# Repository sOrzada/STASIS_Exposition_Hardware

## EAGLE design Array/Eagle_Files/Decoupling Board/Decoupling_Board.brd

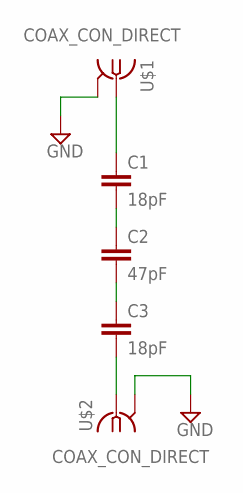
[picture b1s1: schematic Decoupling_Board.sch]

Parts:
C1, C3: 18pF; C1210
C2: 47pF; C1210
U$1, U$2: COAX_CON_DIRECT; COAX.141

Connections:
GND: U$1.P$2 (GND), U$2.P$2 (GND)
unnamed: C1.1, U$1.P$1 (1)
unnamed: C1.2, C2.1
unnamed: C2.2, C3.1
unnamed: C3.2, U$2.P$1 (1)

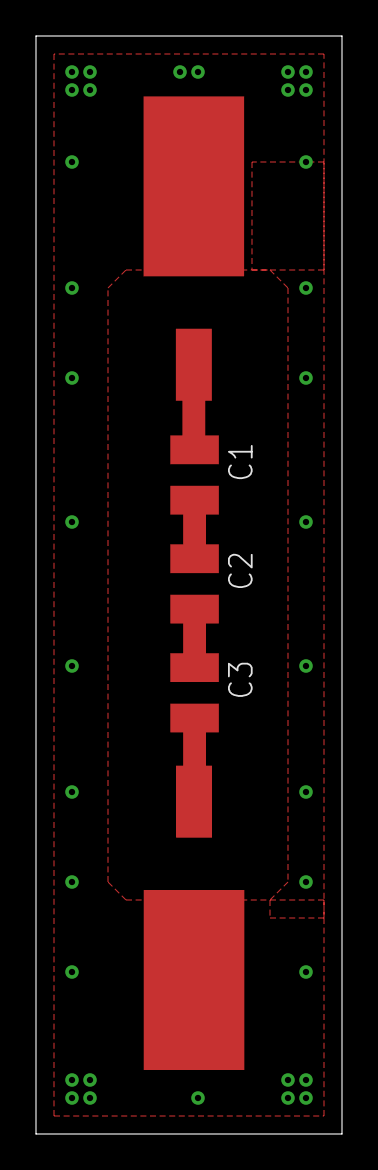
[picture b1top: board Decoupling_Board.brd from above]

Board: 2 copper layers, 17.0 x 61.0 mm, 5 parts (0 on the bottom side), 5 nets.

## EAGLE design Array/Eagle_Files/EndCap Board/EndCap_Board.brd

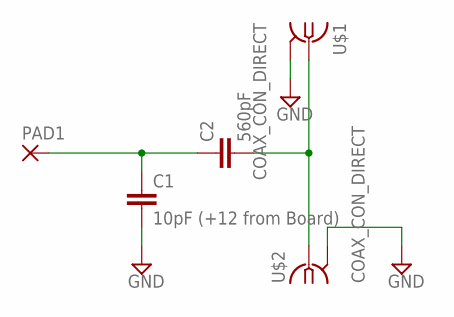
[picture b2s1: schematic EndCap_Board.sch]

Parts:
C1: 10pF (+12 from Board); C1210
C2: 560pF; C1210
PAD1: SMD5; SMD2,54-5,08
U$1, U$2: COAX_CON_DIRECT; COAX.141

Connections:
GND: C1.2, U$1.P$2 (GND), U$2.P$2 (GND)
unnamed: C1.1, C2.1, PAD1.1
unnamed: C2.2, U$1.P$1 (1), U$2.P$1 (1)

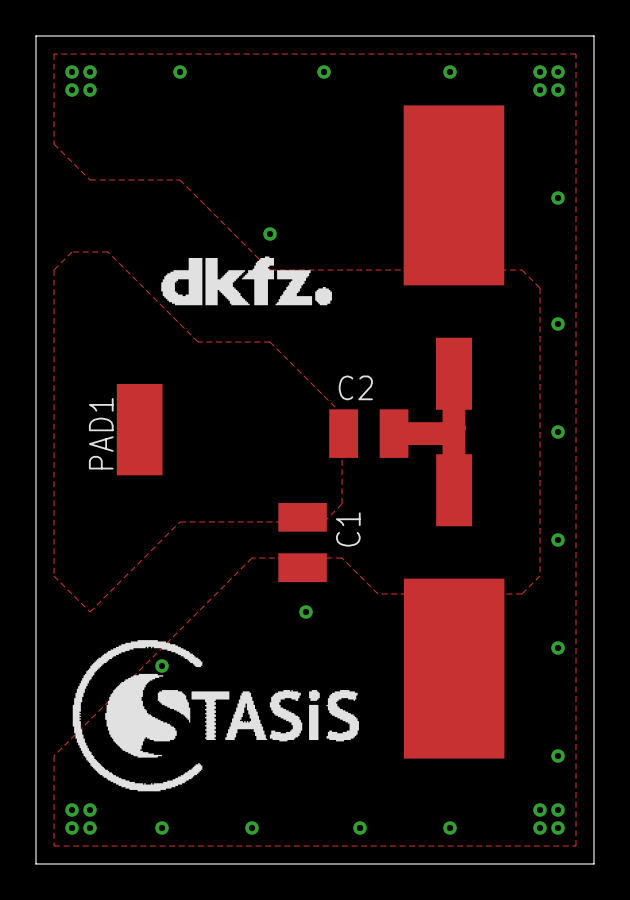
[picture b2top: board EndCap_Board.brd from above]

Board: 2 copper layers, 31.0 x 46.0 mm, 7 parts (0 on the bottom side), 3 nets.

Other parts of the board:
U$3: LOGO_STASIS
U$4: LOGO_DKFZ

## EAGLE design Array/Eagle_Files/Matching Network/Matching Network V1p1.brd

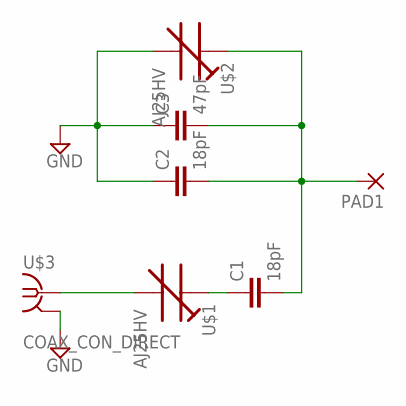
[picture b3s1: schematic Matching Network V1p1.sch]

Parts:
C1, C2: 18pF; C1210
C3: 47pF; C1210
PAD1: SMD5; SMD2,54-5,08
U$1, U$2: AJ25HV
U$3: COAX_CON_DIRECT; COAX.141

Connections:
GND: C2.1, C3.1, U$2.P$1 (A), U$3.P$2 (GND)
unnamed: C1.1, U$1.P$2 (E)
unnamed: C1.2, C2.2, C3.2, PAD1.1, U$2.P$2 (E)
unnamed: U$1.P$1 (A), U$3.P$1 (1)

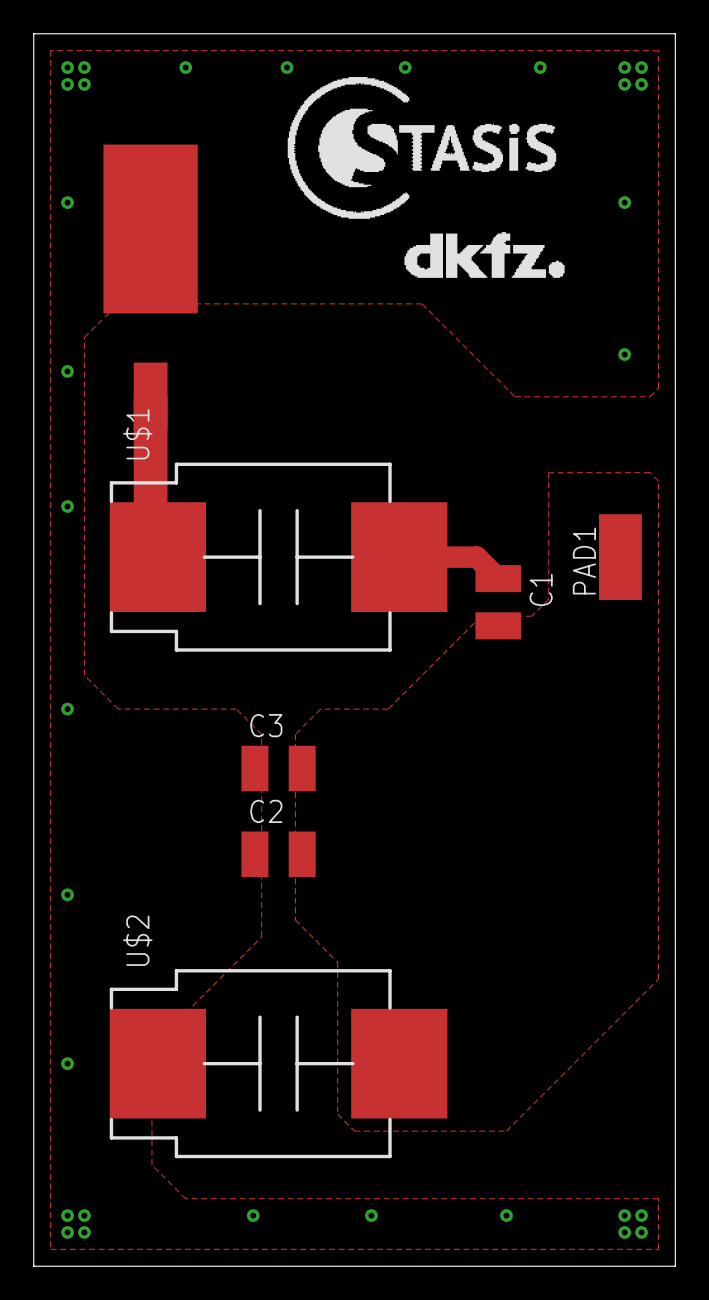
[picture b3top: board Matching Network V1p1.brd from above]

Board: 2 copper layers, 38.0 x 73.0 mm, 9 parts (0 on the bottom side), 4 nets.

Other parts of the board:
U$4: LOGO_STASIS
U$5: LOGO_DKFZ

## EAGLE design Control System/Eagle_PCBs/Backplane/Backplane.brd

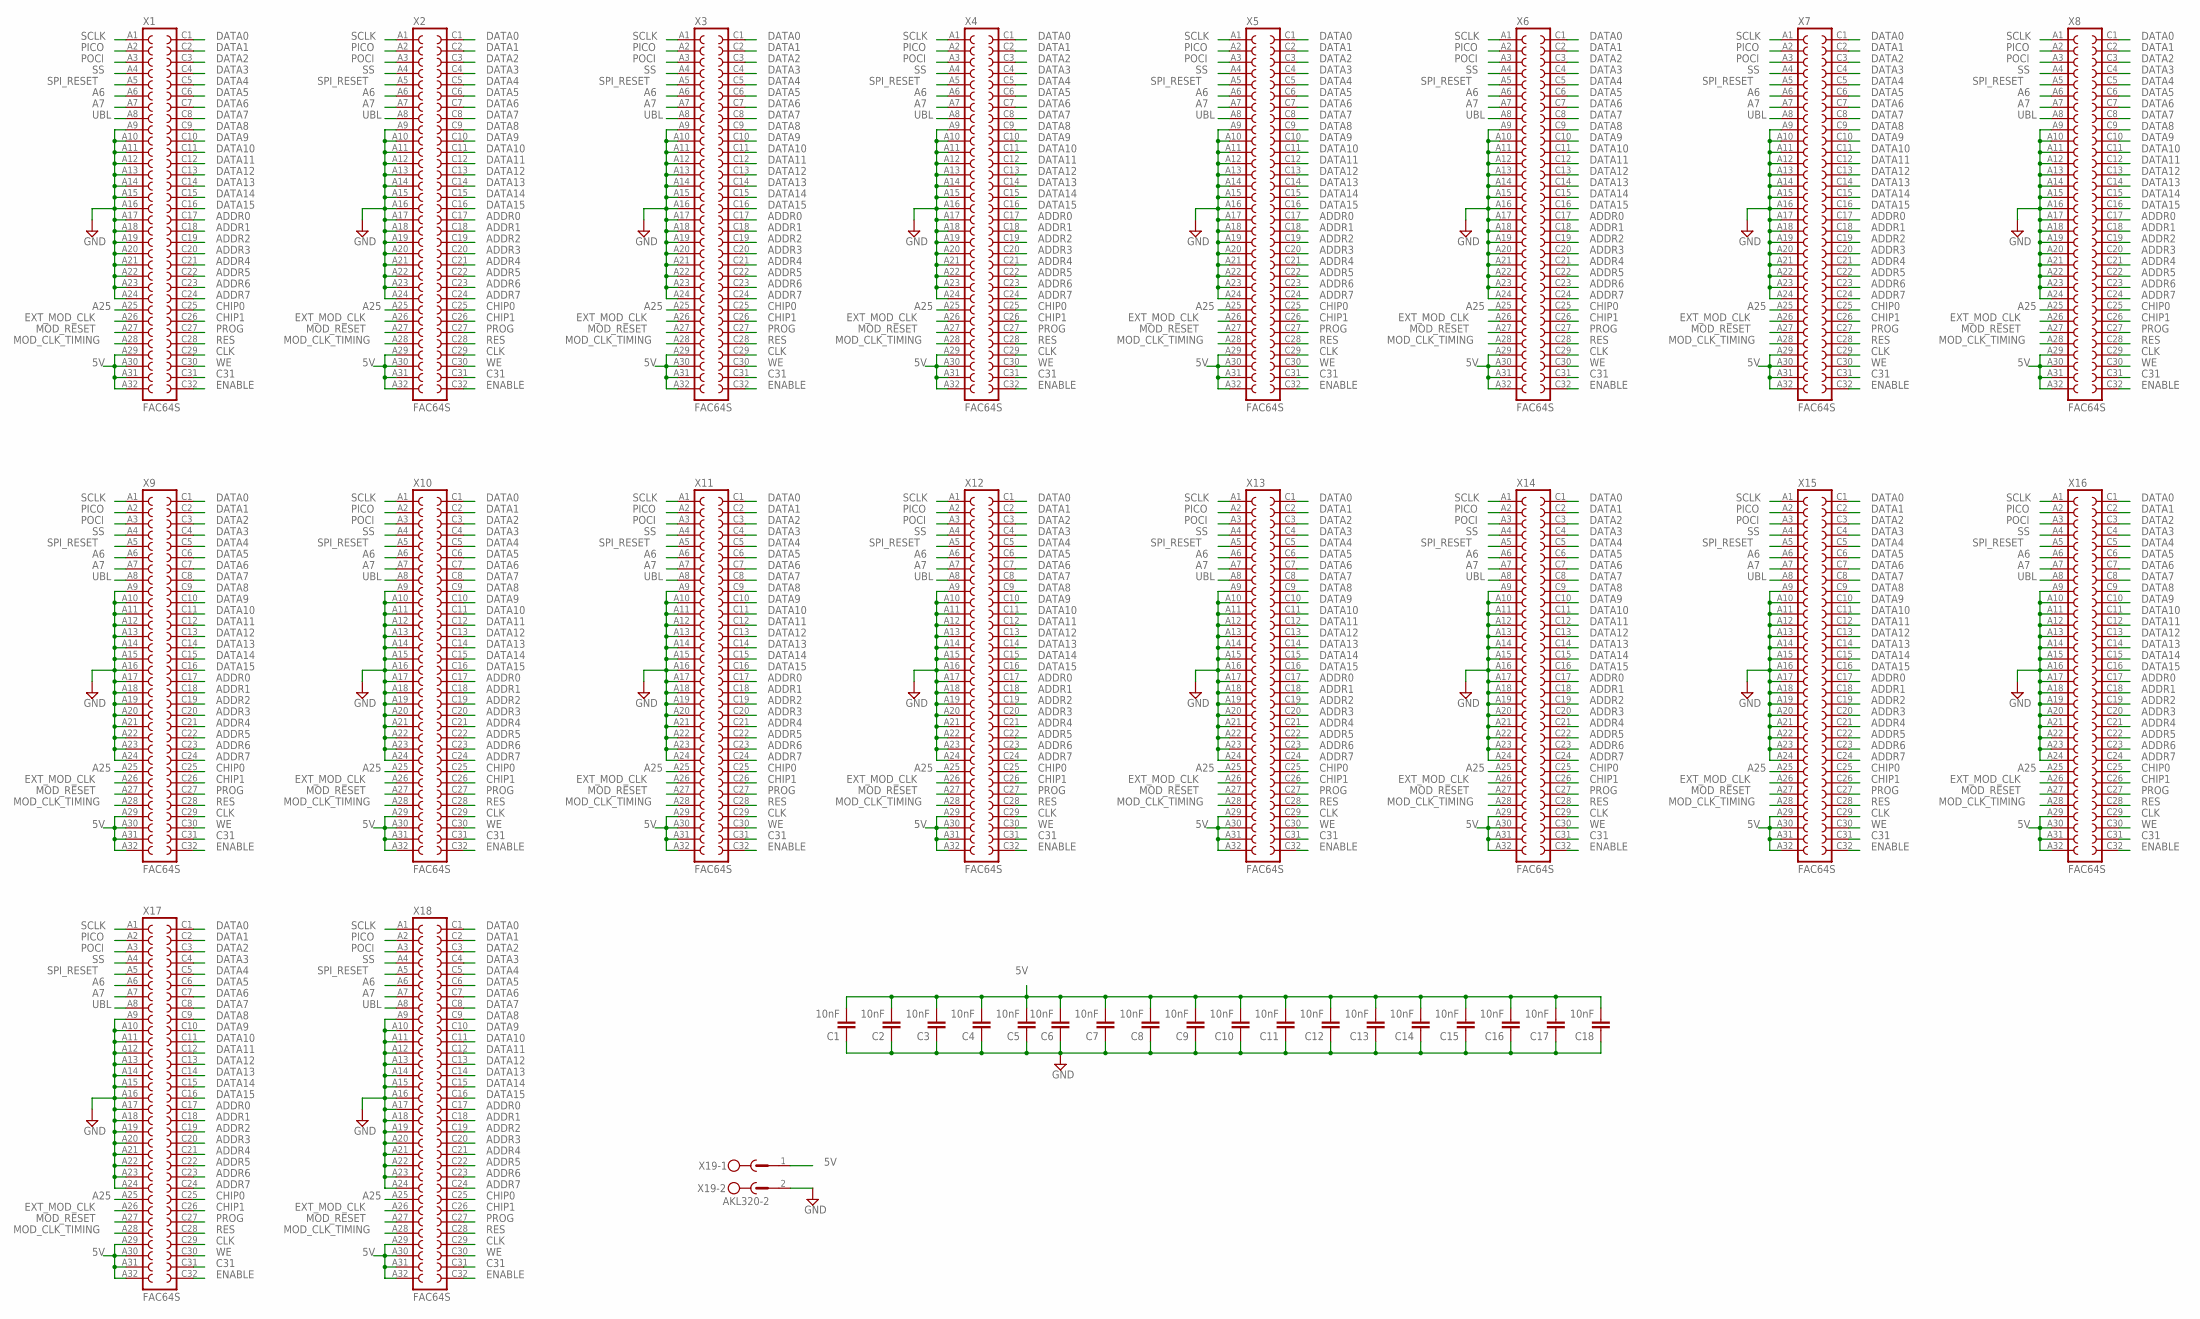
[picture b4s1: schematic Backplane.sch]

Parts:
C1, C2, C3, C4, C5, C6, C7, C8, C9, C10, C11, C12, C13, C14, C15, C16, C17, C18: 10nF; C0603
X1, X2, X3, X4, X5, X6, X7, X8, X9, X10, X11, X12, X13, X14, X15, X16, X17, X18: FAC64S
X19: AKL320-2; MSTBV2

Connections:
5V: C1.2, C2.2, C3.2, C4.2, C5.2, C6.2, C7.2, C8.2, C9.2, C10.2, C11.2, C12.2, C13.2, C14.2, C15.2, C16.2, C17.2, C18.2, X1.A29, X1.A30, X1.A31, X1.A32, X2.A29, X2.A30, X2.A31, X2.A32, X3.A29, X3.A30, X3.A31, X3.A32, X4.A29, X4.A30, X4.A31, X4.A32, X5.A29, X5.A30, X5.A31, X5.A32, X6.A29, X6.A30, X6.A31, X6.A32, X7.A29, X7.A30, X7.A31, X7.A32, X8.A29, X8.A30, X8.A31, X8.A32, X9.A29, X9.A30, X9.A31, X9.A32, X10.A29, X10.A30, X10.A31, X10.A32, X11.A29, X11.A30, X11.A31, X11.A32, X12.A29, X12.A30, X12.A31, X12.A32, X13.A29, X13.A30, X13.A31, X13.A32, X14.A29, X14.A30, X14.A31, X14.A32, X15.A29, X15.A30, X15.A31, X15.A32, X16.A29, X16.A30, X16.A31, X16.A32, X17.A29, X17.A30, X17.A31, X17.A32, X18.A29, X18.A30, X18.A31, X18.A32, X19.1
A6: X1.A6, X2.A6, X3.A6, X4.A6, X5.A6, X6.A6, X7.A6, X8.A6, X9.A6, X10.A6, X11.A6, X12.A6, X13.A6, X14.A6, X15.A6, X16.A6, X17.A6, X18.A6
A7: X1.A7, X2.A7, X3.A7, X4.A7, X5.A7, X6.A7, X7.A7, X8.A7, X9.A7, X10.A7, X11.A7, X12.A7, X13.A7, X14.A7, X15.A7, X16.A7, X17.A7, X18.A7
A25: X1.A25, X2.A25, X3.A25, X4.A25, X5.A25, X6.A25, X7.A25, X8.A25, X9.A25, X10.A25, X11.A25, X12.A25, X13.A25, X14.A25, X15.A25, X16.A25, X17.A25, X18.A25
ADDR0: X1.C17, X2.C17, X3.C17, X4.C17, X5.C17, X6.C17, X7.C17, X8.C17, X9.C17, X10.C17, X11.C17, X12.C17, X13.C17, X14.C17, X15.C17, X16.C17, X17.C17, X18.C17
ADDR1: X1.C18, X2.C18, X3.C18, X4.C18, X5.C18, X6.C18, X7.C18, X8.C18, X9.C18, X10.C18, X11.C18, X12.C18, X13.C18, X14.C18, X15.C18, X16.C18, X17.C18, X18.C18
ADDR2: X1.C19, X2.C19, X3.C19, X4.C19, X5.C19, X6.C19, X7.C19, X8.C19, X9.C19, X10.C19, X11.C19, X12.C19, X13.C19, X14.C19, X15.C19, X16.C19, X17.C19, X18.C19
ADDR3: X1.C20, X2.C20, X3.C20, X4.C20, X5.C20, X6.C20, X7.C20, X8.C20, X9.C20, X10.C20, X11.C20, X12.C20, X13.C20, X14.C20, X15.C20, X16.C20, X17.C20, X18.C20
ADDR4: X1.C21, X2.C21, X3.C21, X4.C21, X5.C21, X6.C21, X7.C21, X8.C21, X9.C21, X10.C21, X11.C21, X12.C21, X13.C21, X14.C21, X15.C21, X16.C21, X17.C21, X18.C21
ADDR5: X1.C22, X2.C22, X3.C22, X4.C22, X5.C22, X6.C22, X7.C22, X8.C22, X9.C22, X10.C22, X11.C22, X12.C22, X13.C22, X14.C22, X15.C22, X16.C22, X17.C22, X18.C22
ADDR6: X1.C23, X2.C23, X3.C23, X4.C23, X5.C23, X6.C23, X7.C23, X8.C23, X9.C23, X10.C23, X11.C23, X12.C23, X13.C23, X14.C23, X15.C23, X16.C23, X17.C23, X18.C23
ADDR7: X1.C24, X2.C24, X3.C24, X4.C24, X5.C24, X6.C24, X7.C24, X8.C24, X9.C24, X10.C24, X11.C24, X12.C24, X13.C24, X14.C24, X15.C24, X16.C24, X17.C24, X18.C24
C31: X1.C31, X2.C31, X3.C31, X4.C31, X5.C31, X6.C31, X7.C31, X8.C31, X9.C31, X10.C31, X11.C31, X12.C31, X13.C31, X14.C31, X15.C31, X16.C31, X17.C31, X18.C31
CHIP0: X1.C25, X2.C25, X3.C25, X4.C25, X5.C25, X6.C25, X7.C25, X8.C25, X9.C25, X10.C25, X11.C25, X12.C25, X13.C25, X14.C25, X15.C25, X16.C25, X17.C25, X18.C25
CHIP1: X1.C26, X2.C26, X3.C26, X4.C26, X5.C26, X6.C26, X7.C26, X8.C26, X9.C26, X10.C26, X11.C26, X12.C26, X13.C26, X14.C26, X15.C26, X16.C26, X17.C26, X18.C26
CLK: X1.C29, X2.C29, X3.C29, X4.C29, X5.C29, X6.C29, X7.C29, X8.C29, X9.C29, X10.C29, X11.C29, X12.C29, X13.C29, X14.C29, X15.C29, X16.C29, X17.C29, X18.C29
DATA0: X1.C1, X2.C1, X3.C1, X4.C1, X5.C1, X6.C1, X7.C1, X8.C1, X9.C1, X10.C1, X11.C1, X12.C1, X13.C1, X14.C1, X15.C1, X16.C1, X17.C1, X18.C1
DATA1: X1.C2, X2.C2, X3.C2, X4.C2, X5.C2, X6.C2, X7.C2, X8.C2, X9.C2, X10.C2, X11.C2, X12.C2, X13.C2, X14.C2, X15.C2, X16.C2, X17.C2, X18.C2
DATA2: X1.C3, X2.C3, X3.C3, X4.C3, X5.C3, X6.C3, X7.C3, X8.C3, X9.C3, X10.C3, X11.C3, X12.C3, X13.C3, X14.C3, X15.C3, X16.C3, X17.C3, X18.C3
DATA3: X1.C4, X2.C4, X3.C4, X4.C4, X5.C4, X6.C4, X7.C4, X8.C4, X9.C4, X10.C4, X11.C4, X12.C4, X13.C4, X14.C4, X15.C4, X16.C4, X17.C4, X18.C4
DATA4: X1.C5, X2.C5, X3.C5, X4.C5, X5.C5, X6.C5, X7.C5, X8.C5, X9.C5, X10.C5, X11.C5, X12.C5, X13.C5, X14.C5, X15.C5, X16.C5, X17.C5, X18.C5
DATA5: X1.C6, X2.C6, X3.C6, X4.C6, X5.C6, X6.C6, X7.C6, X8.C6, X9.C6, X10.C6, X11.C6, X12.C6, X13.C6, X14.C6, X15.C6, X16.C6, X17.C6, X18.C6
DATA6: X1.C7, X2.C7, X3.C7, X4.C7, X5.C7, X6.C7, X7.C7, X8.C7, X9.C7, X10.C7, X11.C7, X12.C7, X13.C7, X14.C7, X15.C7, X16.C7, X17.C7, X18.C7
DATA7: X1.C8, X2.C8, X3.C8, X4.C8, X5.C8, X6.C8, X7.C8, X8.C8, X9.C8, X10.C8, X11.C8, X12.C8, X13.C8, X14.C8, X15.C8, X16.C8, X17.C8, X18.C8
DATA8: X1.C9, X2.C9, X3.C9, X4.C9, X5.C9, X6.C9, X7.C9, X8.C9, X9.C9, X10.C9, X11.C9, X12.C9, X13.C9, X14.C9, X15.C9, X16.C9, X17.C9, X18.C9
DATA9: X1.C10, X2.C10, X3.C10, X4.C10, X5.C10, X6.C10, X7.C10, X8.C10, X9.C10, X10.C10, X11.C10, X12.C10, X13.C10, X14.C10, X15.C10, X16.C10, X17.C10, X18.C10
DATA10: X1.C11, X2.C11, X3.C11, X4.C11, X5.C11, X6.C11, X7.C11, X8.C11, X9.C11, X10.C11, X11.C11, X12.C11, X13.C11, X14.C11, X15.C11, X16.C11, X17.C11, X18.C11
DATA11: X1.C12, X2.C12, X3.C12, X4.C12, X5.C12, X6.C12, X7.C12, X8.C12, X9.C12, X10.C12, X11.C12, X12.C12, X13.C12, X14.C12, X15.C12, X16.C12, X17.C12, X18.C12
DATA12: X1.C13, X2.C13, X3.C13, X4.C13, X5.C13, X6.C13, X7.C13, X8.C13, X9.C13, X10.C13, X11.C13, X12.C13, X13.C13, X14.C13, X15.C13, X16.C13, X17.C13, X18.C13
DATA13: X1.C14, X2.C14, X3.C14, X4.C14, X5.C14, X6.C14, X7.C14, X8.C14, X9.C14, X10.C14, X11.C14, X12.C14, X13.C14, X14.C14, X15.C14, X16.C14, X17.C14, X18.C14
DATA14: X1.C15, X2.C15, X3.C15, X4.C15, X5.C15, X6.C15, X7.C15, X8.C15, X9.C15, X10.C15, X11.C15, X12.C15, X13.C15, X14.C15, X15.C15, X16.C15, X17.C15, X18.C15
DATA15: X1.C16, X2.C16, X3.C16, X4.C16, X5.C16, X6.C16, X7.C16, X8.C16, X9.C16, X10.C16, X11.C16, X12.C16, X13.C16, X14.C16, X15.C16, X16.C16, X17.C16, X18.C16
ENABLE: X1.C32, X2.C32, X3.C32, X4.C32, X5.C32, X6.C32, X7.C32, X8.C32, X9.C32, X10.C32, X11.C32, X12.C32, X13.C32, X14.C32, X15.C32, X16.C32, X17.C32, X18.C32
EXT_MOD_CLK: X1.A26, X2.A26, X3.A26, X4.A26, X5.A26, X6.A26, X7.A26, X8.A26, X9.A26, X10.A26, X11.A26, X12.A26, X13.A26, X14.A26, X15.A26, X16.A26, X17.A26, X18.A26
GND: C1.1, C2.1, C3.1, C4.1, C5.1, C6.1, C7.1, C8.1, C9.1, C10.1, C11.1, C12.1, C13.1, C14.1, C15.1, C16.1, C17.1, C18.1, X1.A9, X1.A10, X1.A11, X1.A12, X1.A13, X1.A14, X1.A15, X1.A16, X1.A17, X1.A18, X1.A19, X1.A20, X1.A21, X1.A22, X1.A23, X1.A24, X2.A9, X2.A10, X2.A11, X2.A12, X2.A13, X2.A14, X2.A15, X2.A16, X2.A17, X2.A18, X2.A19, X2.A20, X2.A21, X2.A22, X2.A23, X2.A24, X3.A9, X3.A10, X3.A11, X3.A12, X3.A13, X3.A14, X3.A15, X3.A16, X3.A17, X3.A18, X3.A19, X3.A20, X3.A21, X3.A22, X3.A23, X3.A24, X4.A9, X4.A10, X4.A11, X4.A12, X4.A13, X4.A14, X4.A15, X4.A16, X4.A17, X4.A18, X4.A19, X4.A20, X4.A21, X4.A22, X4.A23, X4.A24, X5.A9, X5.A10, X5.A11, X5.A12, X5.A13, X5.A14, X5.A15, X5.A16, X5.A17, X5.A18, X5.A19, X5.A20, X5.A21, X5.A22, X5.A23, X5.A24, X6.A9, X6.A10, X6.A11, X6.A12, X6.A13, X6.A14, X6.A15, X6.A16, X6.A17, X6.A18, X6.A19, X6.A20, X6.A21, X6.A22, X6.A23, X6.A24, X7.A9, X7.A10, X7.A11, X7.A12, X7.A13, X7.A14, X7.A15, X7.A16, X7.A17, X7.A18, X7.A19, X7.A20, X7.A21, X7.A22, X7.A23, X7.A24, X8.A9, X8.A10, X8.A11, X8.A12, X8.A13, X8.A14, X8.A15, X8.A16, X8.A17, X8.A18, X8.A19, X8.A20, X8.A21, X8.A22, X8.A23, X8.A24, X9.A9, X9.A10, X9.A11, X9.A12, X9.A13, X9.A14, X9.A15, X9.A16, X9.A17, X9.A18, X9.A19, X9.A20, X9.A21, X9.A22, X9.A23, X9.A24, X10.A9, X10.A10, X10.A11, X10.A12, X10.A13, X10.A14, X10.A15, X10.A16, X10.A17, X10.A18, X10.A19, X10.A20, X10.A21, X10.A22, X10.A23, X10.A24, X11.A9, X11.A10, X11.A11, X11.A12, X11.A13, X11.A14, X11.A15, X11.A16, X11.A17, X11.A18, X11.A19, X11.A20, X11.A21, X11.A22, X11.A23, X11.A24, X12.A9, X12.A10, X12.A11, X12.A12, X12.A13, X12.A14, X12.A15, X12.A16, X12.A17, X12.A18, X12.A19, X12.A20, X12.A21, X12.A22, X12.A23, X12.A24, X13.A9, X13.A10, X13.A11, X13.A12, X13.A13, X13.A14, X13.A15, X13.A16, X13.A17, X13.A18, X13.A19, X13.A20, X13.A21, X13.A22, X13.A23, X13.A24, X14.A9, X14.A10, X14.A11, X14.A12, X14.A13, X14.A14, X14.A15, X14.A16, X14.A17, X14.A18, X14.A19, X14.A20, X14.A21, X14.A22, X14.A23, X14.A24, X15.A9, X15.A10, X15.A11, X15.A12, X15.A13, X15.A14, X15.A15, X15.A16, X15.A17, X15.A18, X15.A19, X15.A20, X15.A21, X15.A22, X15.A23, X15.A24, X16.A9, X16.A10, X16.A11, X16.A12, X16.A13, X16.A14, X16.A15, X16.A16, X16.A17, X16.A18, X16.A19, X16.A20, X16.A21, X16.A22, X16.A23, X16.A24, X17.A9, X17.A10, X17.A11, X17.A12, X17.A13, X17.A14, X17.A15, X17.A16, X17.A17, X17.A18, X17.A19, X17.A20, X17.A21, X17.A22, X17.A23, X17.A24, X18.A9, X18.A10, X18.A11, X18.A12, X18.A13, X18.A14, X18.A15, X18.A16, X18.A17, X18.A18, X18.A19, X18.A20, X18.A21, X18.A22, X18.A23, X18.A24, X19.2
MOD_CLK_TIMING: X1.A28, X2.A28, X3.A28, X4.A28, X5.A28, X6.A28, X7.A28, X8.A28, X9.A28, X10.A28, X11.A28, X12.A28, X13.A28, X14.A28, X15.A28, X16.A28, X17.A28, X18.A28
MOD_RESET: X1.A27, X2.A27, X3.A27, X4.A27, X5.A27, X6.A27, X7.A27, X8.A27, X9.A27, X10.A27, X11.A27, X12.A27, X13.A27, X14.A27, X15.A27, X16.A27, X17.A27, X18.A27
PICO: X1.A2, X2.A2, X3.A2, X4.A2, X5.A2, X6.A2, X7.A2, X8.A2, X9.A2, X10.A2, X11.A2, X12.A2, X13.A2, X14.A2, X15.A2, X16.A2, X17.A2, X18.A2
POCI: X1.A3, X2.A3, X3.A3, X4.A3, X5.A3, X6.A3, X7.A3, X8.A3, X9.A3, X10.A3, X11.A3, X12.A3, X13.A3, X14.A3, X15.A3, X16.A3, X17.A3, X18.A3
PROG: X1.C27, X2.C27, X3.C27, X4.C27, X5.C27, X6.C27, X7.C27, X8.C27, X9.C27, X10.C27, X11.C27, X12.C27, X13.C27, X14.C27, X15.C27, X16.C27, X17.C27, X18.C27
RES: X1.C28, X2.C28, X3.C28, X4.C28, X5.C28, X6.C28, X7.C28, X8.C28, X9.C28, X10.C28, X11.C28, X12.C28, X13.C28, X14.C28, X15.C28, X16.C28, X17.C28, X18.C28
SCLK: X1.A1, X2.A1, X3.A1, X4.A1, X5.A1, X6.A1, X7.A1, X8.A1, X9.A1, X10.A1, X11.A1, X12.A1, X13.A1, X14.A1, X15.A1, X16.A1, X17.A1, X18.A1
SPI_RESET: X1.A5, X2.A5, X3.A5, X4.A5, X5.A5, X6.A5, X7.A5, X8.A5, X9.A5, X10.A5, X11.A5, X12.A5, X13.A5, X14.A5, X15.A5, X16.A5, X17.A5, X18.A5
SS: X1.A4, X2.A4, X3.A4, X4.A4, X5.A4, X6.A4, X7.A4, X8.A4, X9.A4, X10.A4, X11.A4, X12.A4, X13.A4, X14.A4, X15.A4, X16.A4, X17.A4, X18.A4
UBL: X1.A8, X2.A8, X3.A8, X4.A8, X5.A8, X6.A8, X7.A8, X8.A8, X9.A8, X10.A8, X11.A8, X12.A8, X13.A8, X14.A8, X15.A8, X16.A8, X17.A8, X18.A8
WE: X1.C30, X2.C30, X3.C30, X4.C30, X5.C30, X6.C30, X7.C30, X8.C30, X9.C30, X10.C30, X11.C30, X12.C30, X13.C30, X14.C30, X15.C30, X16.C30, X17.C30, X18.C30

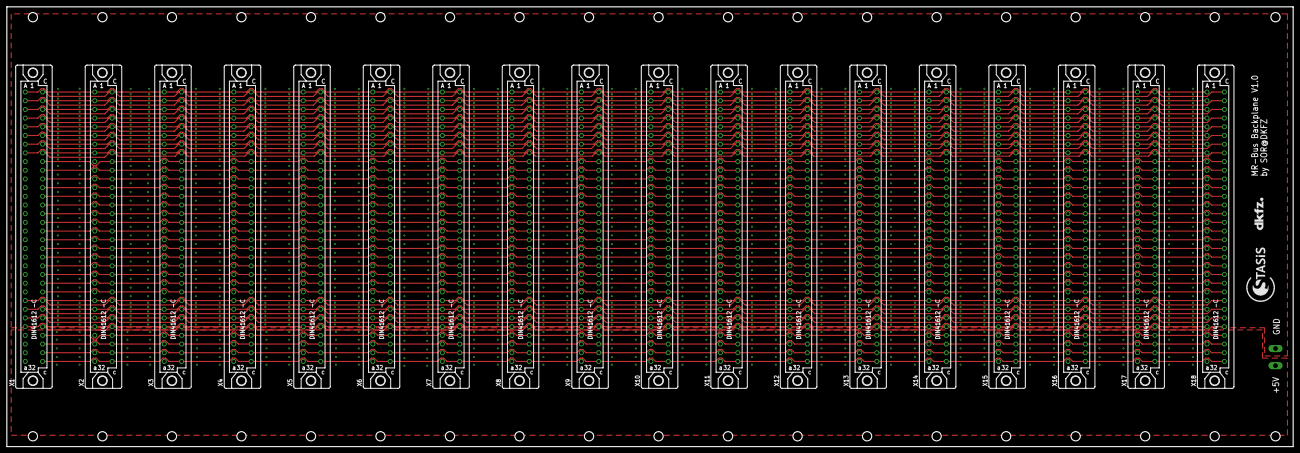
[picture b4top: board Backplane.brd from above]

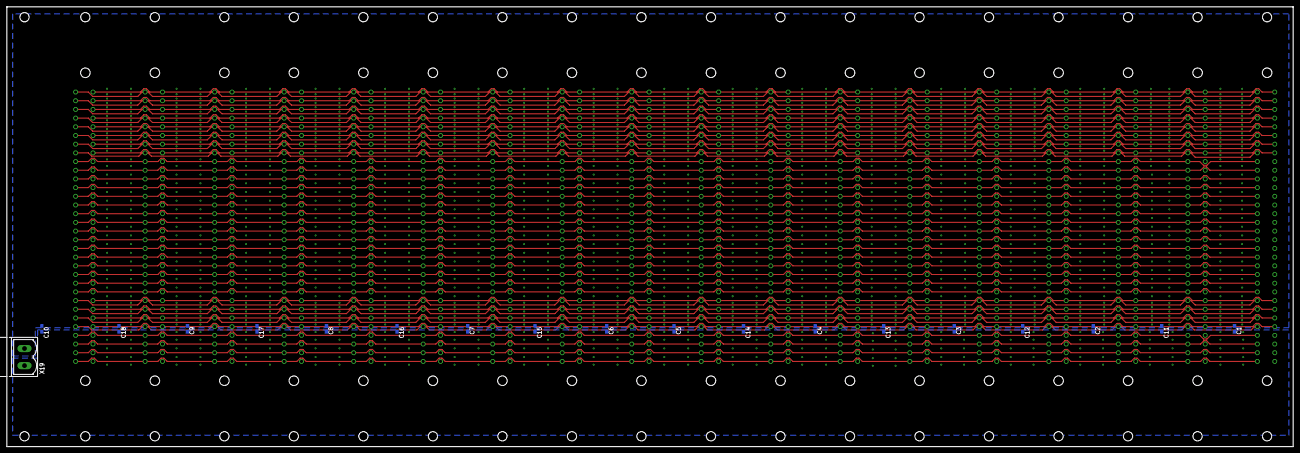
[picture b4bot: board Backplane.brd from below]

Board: 2 copper layers, 376.0 x 128.6 mm, 39 parts (19 on the bottom side), 46 nets.

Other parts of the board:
U$1: LOGO_STASIS
U$2: LOGO_DKFZ

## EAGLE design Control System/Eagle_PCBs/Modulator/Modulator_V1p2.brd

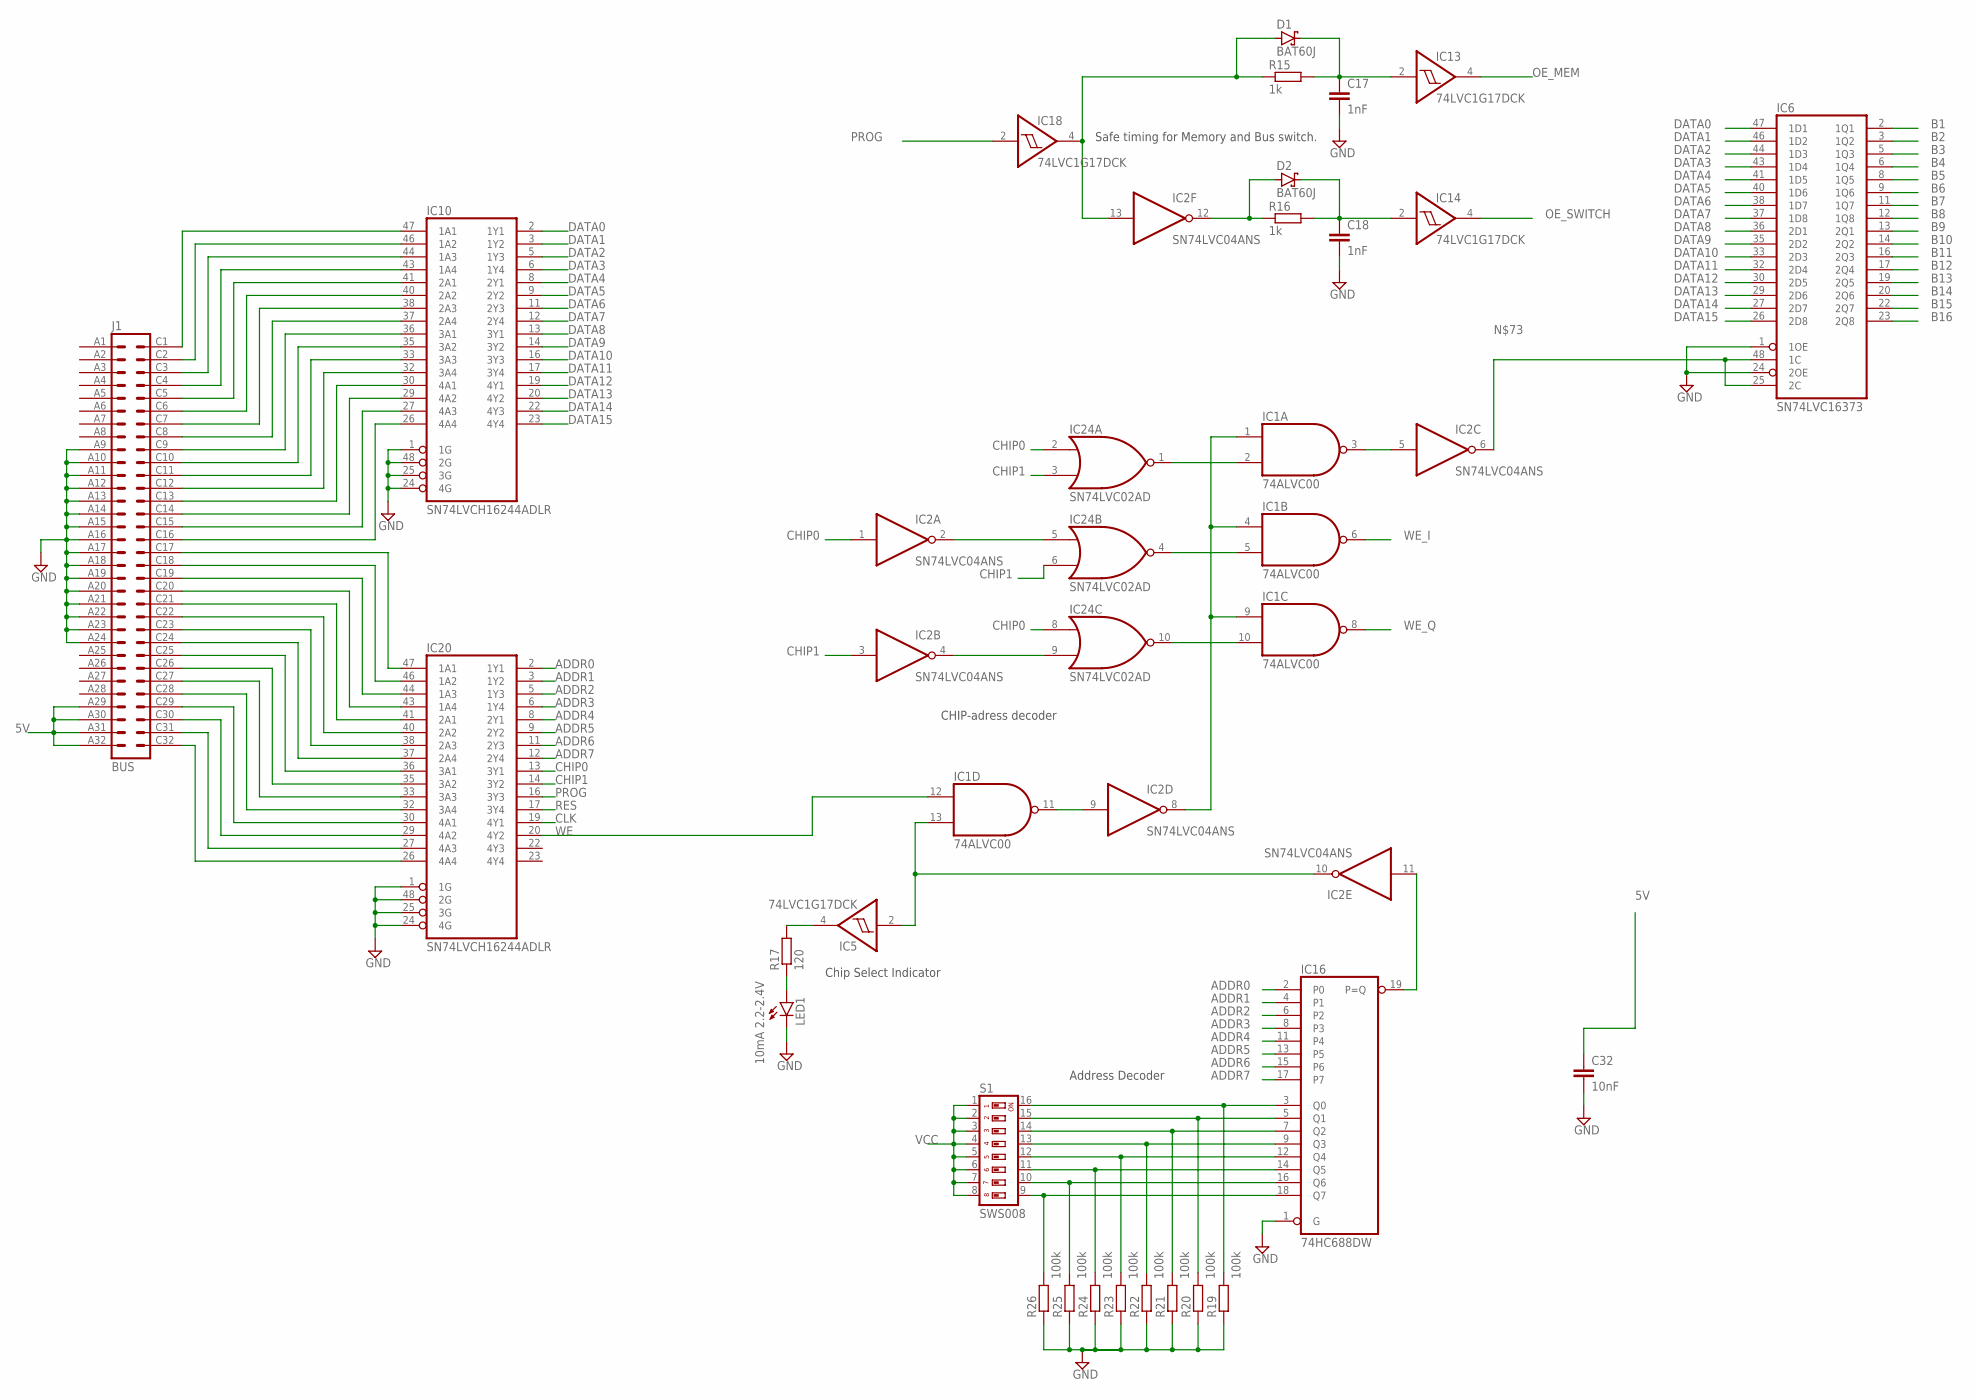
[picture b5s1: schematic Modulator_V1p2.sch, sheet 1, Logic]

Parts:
C17, C18: 1nF; C0805
C32: 10nF; C0603
D1, D2: BAT60J; SOD323_ST
IC1: 74ALVC00; SO14
IC2: SN74LVC04ANS; SO14
IC5, IC13, IC14, IC18: 74LVC1G17DCK; SC70-5
IC6: SN74LVC16373; SSOP48DL
IC10, IC20: SN74LVCH16244ADLR; SSOP48DL
IC16: 74HC688DW; SO20W
IC24: SN74LVC02AD; SO14
J1: BUS; VG64B
LED1: 10mA 2.2-2.4V; LED3MM
R15, R16: 1k; R0603
R17: 120; R0603
R19, R20, R21, R22, R23, R24, R25, R26: 100k; R0603
S1: SWS008; SMS-008

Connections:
5V: C32.1, J1.A29, J1.A30, J1.A31, J1.A32; also elsewhere on the board
ADDR0: IC16.2 (P0), IC20.2 (1Y1)
ADDR1: IC16.4 (P1), IC20.3 (1Y2)
ADDR2: IC16.6 (P2), IC20.5 (1Y3)
ADDR3: IC16.8 (P3), IC20.6 (1Y4)
ADDR4: IC16.11 (P4), IC20.8 (2Y1)
ADDR5: IC16.13 (P5), IC20.9 (2Y2)
ADDR6: IC16.15 (P6), IC20.11 (2Y3)
ADDR7: IC16.17 (P7), IC20.12 (2Y4)
B1: IC6.2 (1Q1); also elsewhere on the board
B2: IC6.3 (1Q2); also elsewhere on the board
B3: IC6.5 (1Q3); also elsewhere on the board
B4: IC6.6 (1Q4); also elsewhere on the board
B5: IC6.8 (1Q5); also elsewhere on the board
B6: IC6.9 (1Q6); also elsewhere on the board
B7: IC6.11 (1Q7); also elsewhere on the board
B8: IC6.12 (1Q8); also elsewhere on the board
B9: IC6.13 (2Q1); also elsewhere on the board
B10: IC6.14 (2Q2); also elsewhere on the board
B11: IC6.16 (2Q3); also elsewhere on the board
B12: IC6.17 (2Q4); also elsewhere on the board
B13: IC6.19 (2Q5); also elsewhere on the board
B14: IC6.20 (2Q6); also elsewhere on the board
B15: IC6.22 (2Q7); also elsewhere on the board
B16: IC6.23 (2Q8); also elsewhere on the board
CHIP0: IC2.1 (I), IC20.13 (3Y1), IC24.2 (I0), IC24.8 (I0)
CHIP1: IC2.3 (I), IC20.14 (3Y2), IC24.3 (I1), IC24.6 (I1)
CLK: IC20.19 (4Y1); also elsewhere on the board
DATA0: IC6.47 (1D1), IC10.2 (1Y1); also elsewhere on the board
DATA1: IC6.46 (1D2), IC10.3 (1Y2); also elsewhere on the board
DATA2: IC6.44 (1D3), IC10.5 (1Y3); also elsewhere on the board
DATA3: IC6.43 (1D4), IC10.6 (1Y4); also elsewhere on the board
DATA4: IC6.41 (1D5), IC10.8 (2Y1); also elsewhere on the board
DATA5: IC6.40 (1D6), IC10.9 (2Y2); also elsewhere on the board
DATA6: IC6.38 (1D7), IC10.11 (2Y3); also elsewhere on the board
DATA7: IC6.37 (1D8), IC10.12 (2Y4); also elsewhere on the board
DATA8: IC6.36 (2D1), IC10.13 (3Y1); also elsewhere on the board
DATA9: IC6.35 (2D2), IC10.14 (3Y2); also elsewhere on the board
DATA10: IC6.33 (2D3), IC10.16 (3Y3); also elsewhere on the board
DATA11: IC6.32 (2D4), IC10.17 (3Y4); also elsewhere on the board
DATA12: IC6.30 (2D5), IC10.19 (4Y1); also elsewhere on the board
DATA13: IC6.29 (2D6), IC10.20 (4Y2); also elsewhere on the board
DATA14: IC6.27 (2D7), IC10.22 (4Y3); also elsewhere on the board
DATA15: IC6.26 (2D8), IC10.23 (4Y4); also elsewhere on the board
GND: C17.2, C18.2, C32.2, IC1.7 (GND), IC2.7 (GND), IC5.3 (GND), IC6.1 (1OE), IC6.4 (GND), IC6.10 (GND), IC6.15 (GND), IC6.21 (GND), IC6.24 (2OE), IC6.28 (GND), IC6.34 (GND), IC6.39 (GND), IC6.45 (GND), IC10.1 (1G), IC10.4 (GND), IC10.10 (GND), IC10.15 (GND), IC10.21 (GND), IC10.24 (4G), IC10.25 (3G), IC10.28 (GND), IC10.34 (GND), IC10.39 (GND), IC10.45 (GND), IC10.48 (2G), IC13.3 (GND), IC14.3 (GND), IC16.1 (G), IC16.10 (GND), IC18.3 (GND), IC20.1 (1G), IC20.4 (GND), IC20.10 (GND), IC20.15 (GND), IC20.21 (GND), IC20.24 (4G), IC20.25 (3G), IC20.28 (GND), IC20.34 (GND), IC20.39 (GND), IC20.45 (GND), IC20.48 (2G), IC24.7 (GND), J1.A9, J1.A10, J1.A11, J1.A12, J1.A13, J1.A14, J1.A15, J1.A16, J1.A17, J1.A18, J1.A19, J1.A20, J1.A21, J1.A22, J1.A23, J1.A24, LED1.K (C), R19.1, R20.1, R21.1, R22.1, R23.1, R24.1, R25.1, R26.1; also elsewhere on the board
unnamed: IC10.47 (1A1), J1.C1
unnamed: IC10.46 (1A2), J1.C2
unnamed: C17.1, D1.C, IC13.2 (I), R15.2
unnamed: IC10.44 (1A3), J1.C3
unnamed: IC10.43 (1A4), J1.C4
unnamed: IC10.41 (2A1), J1.C5
unnamed: IC10.40 (2A2), J1.C6
unnamed: IC10.38 (2A3), J1.C7
unnamed: IC10.37 (2A4), J1.C8
unnamed: IC10.36 (3A1), J1.C9
unnamed: IC10.35 (3A2), J1.C10
unnamed: IC10.33 (3A3), J1.C11
unnamed: IC10.32 (3A4), J1.C12
unnamed: IC10.30 (4A1), J1.C13
unnamed: IC10.29 (4A2), J1.C14
unnamed: IC10.27 (4A3), J1.C15
unnamed: IC10.26 (4A4), J1.C16
unnamed: IC20.47 (1A1), J1.C17
unnamed: IC20.46 (1A2), J1.C18
unnamed: IC20.44 (1A3), J1.C19
unnamed: IC20.43 (1A4), J1.C20
unnamed: IC20.41 (2A1), J1.C21
unnamed: IC20.40 (2A2), J1.C22
unnamed: IC20.38 (2A3), J1.C23
unnamed: IC20.37 (2A4), J1.C24
unnamed: IC20.36 (3A1), J1.C25
unnamed: IC20.35 (3A2), J1.C26
unnamed: IC20.33 (3A3), J1.C27
unnamed: IC16.3 (Q0), R19.2, S1.16
unnamed: C18.1, D2.C, IC14.2 (I), R16.2
unnamed: D2.A, IC2.12 (O), R16.1
unnamed: IC16.5 (Q1), R20.2, S1.15
unnamed: IC16.7 (Q2), R21.2, S1.14
unnamed: IC16.9 (Q3), R22.2, S1.13
unnamed: IC16.12 (Q4), R23.2, S1.12
unnamed: IC16.14 (Q5), R24.2, S1.11
unnamed: IC16.16 (Q6), R25.2, S1.10
unnamed: IC16.18 (Q7), R26.2, S1.9
unnamed: IC1.2 (I1), IC24.1 (O)
unnamed: IC1.5 (I1), IC24.4 (O)
unnamed: IC2.6 (O), IC6.25 (2C), IC6.48 (1C)
unnamed: D1.A, IC2.13 (I), IC18.4 (O), R15.1
unnamed: IC2.2 (O), IC24.5 (I0)
unnamed: IC2.4 (O), IC24.9 (I1)
unnamed: IC20.32 (3A4), J1.C28
unnamed: IC1.10 (I1), IC24.10 (O)
unnamed: IC1.3 (O), IC2.5 (I)
unnamed: IC2.11 (I), IC16.19 (P=Q)
unnamed: IC1.13 (I1), IC2.10 (O), IC5.2 (I)
unnamed: IC1.1 (I0), IC1.4 (I0), IC1.9 (I0), IC2.8 (O)
unnamed: IC1.11 (O), IC2.9 (I)
unnamed: IC20.30 (4A1), J1.C29
unnamed: IC20.29 (4A2), J1.C30
unnamed: IC20.27 (4A3), J1.C31
unnamed: IC20.26 (4A4), J1.C32
unnamed: LED1.A, R17.1
unnamed: IC5.4 (O), R17.2
OE_MEM: IC13.4 (O); also elsewhere on the board
OE_SWITCH: IC14.4 (O); also elsewhere on the board
PROG: IC18.2 (I), IC20.16 (3Y3)
RES: IC20.17 (3Y4); also elsewhere on the board
VCC: IC1.14 (VCC), IC2.14 (VCC), IC5.5 (VCC), IC6.7 (VCC), IC6.18 (VCC), IC6.31 (VCC), IC6.42 (VCC), IC10.7 (VCC), IC10.18 (VCC), IC10.31 (VCC), IC10.42 (VCC), IC13.5 (VCC), IC14.5 (VCC), IC16.20 (VCC), IC18.5 (VCC), IC20.7 (VCC), IC20.18 (VCC), IC20.31 (VCC), IC20.42 (VCC), IC24.14 (VCC), S1.1, S1.2, S1.3, S1.4, S1.5, S1.6, S1.7, S1.8; also elsewhere on the board
WE: IC1.12 (I0), IC20.20 (4Y2)
WE_I: IC1.6 (O); also elsewhere on the board
WE_Q: IC1.8 (O); also elsewhere on the board

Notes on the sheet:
Safe timing for Memory and Bus switch.
CHIP-adress decoder
Address Decoder
Chip Select Indicator
